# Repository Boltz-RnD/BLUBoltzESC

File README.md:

# DarkESC

A Remixed Board Design from The BlueESC with a large footprint and Utilizing easy to source components for a DIYer.

I've made this ESC Board Design for a College Project,but you can use it wherever however you want.

Although it may look a DIY Design but is no diffrent than a 60A version of BlueESC, It runs on a Forked Version of Simonk's TGY firmware.

Unlike other DIY ESC, This one is a lot more reliable and is much more Optimized (Thanks to the TGY Firmware). 

The Firmware for this ESC is same as that of BlueESC and can be found at https://github.com/bluerobotics/tgy

Feel Free to Contribute and develop A better smaller but still DIY-able ESC.

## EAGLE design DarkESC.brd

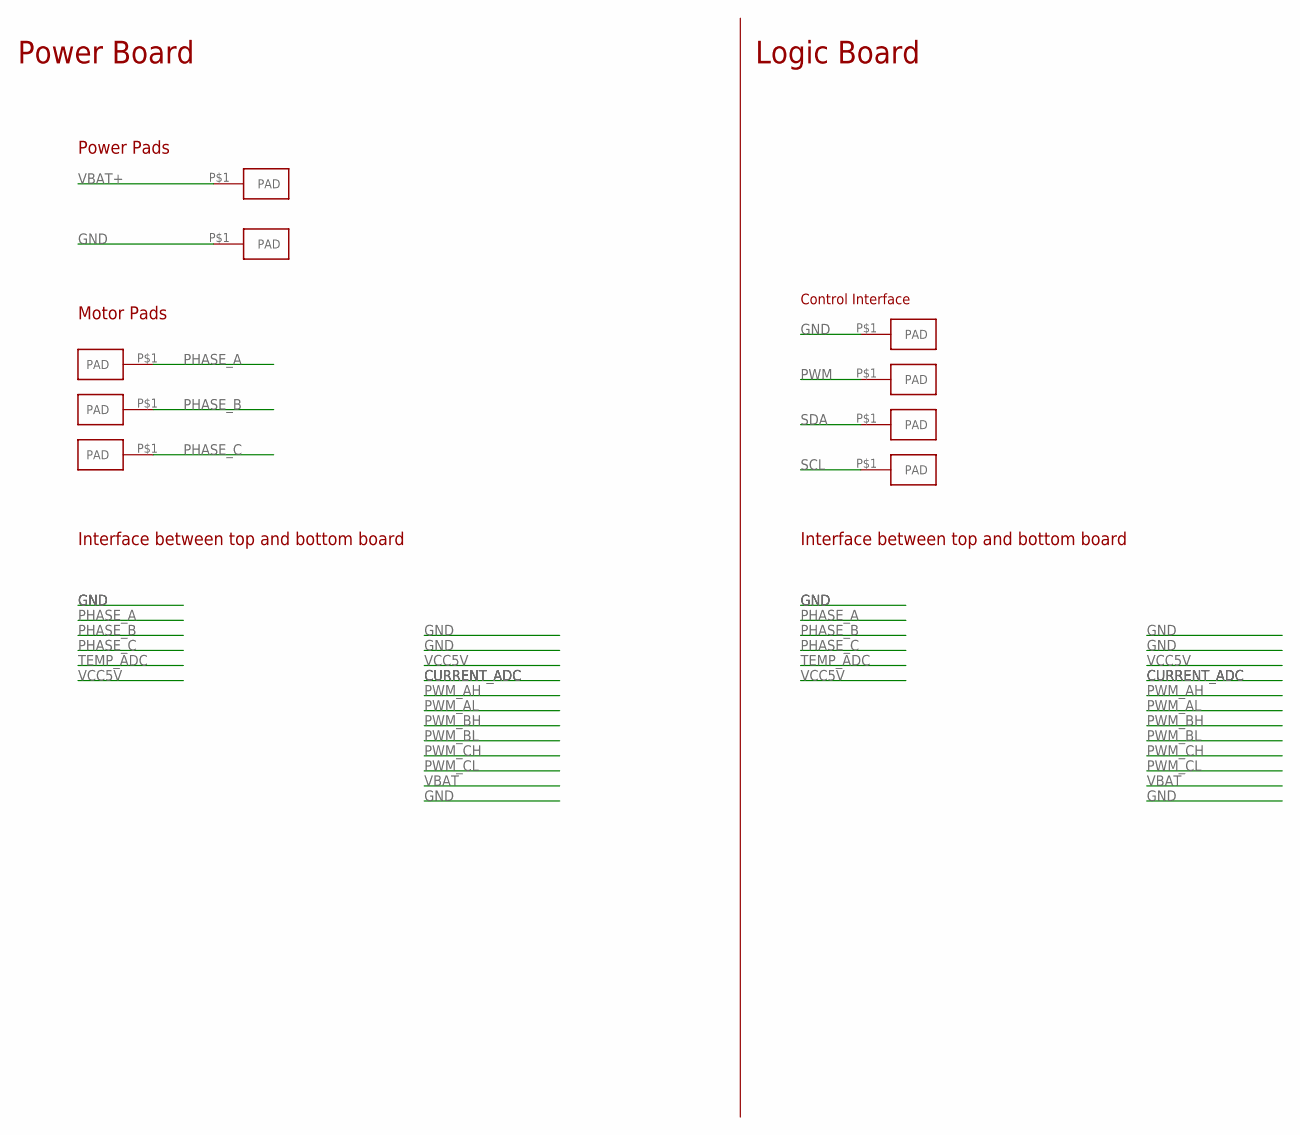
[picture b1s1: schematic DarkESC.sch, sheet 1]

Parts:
U$1, U$2: PADPTH-MED; PAD-PTH-MED-1
U$5, U$6, U$7: PAD18AWG; PAD-PTH-18AWG-1
U$11, U$12, U$13, U$14: PAD1.5X3MM; PAD-1.5X3MM

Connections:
GND: U$2.P$1, U$11.P$1; also elsewhere on the board
PHASE_A: U$5.P$1; also elsewhere on the board
PHASE_B: U$6.P$1; also elsewhere on the board
PHASE_C: U$7.P$1; also elsewhere on the board
PWM: U$14.P$1; also elsewhere on the board
SCL: U$13.P$1; also elsewhere on the board
SDA: U$12.P$1; also elsewhere on the board
VBAT+: U$1.P$1; also elsewhere on the board

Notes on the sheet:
Power Pads
Motor Pads
Interface between top and bottom board
Control Interface
Power Board
Logic Board

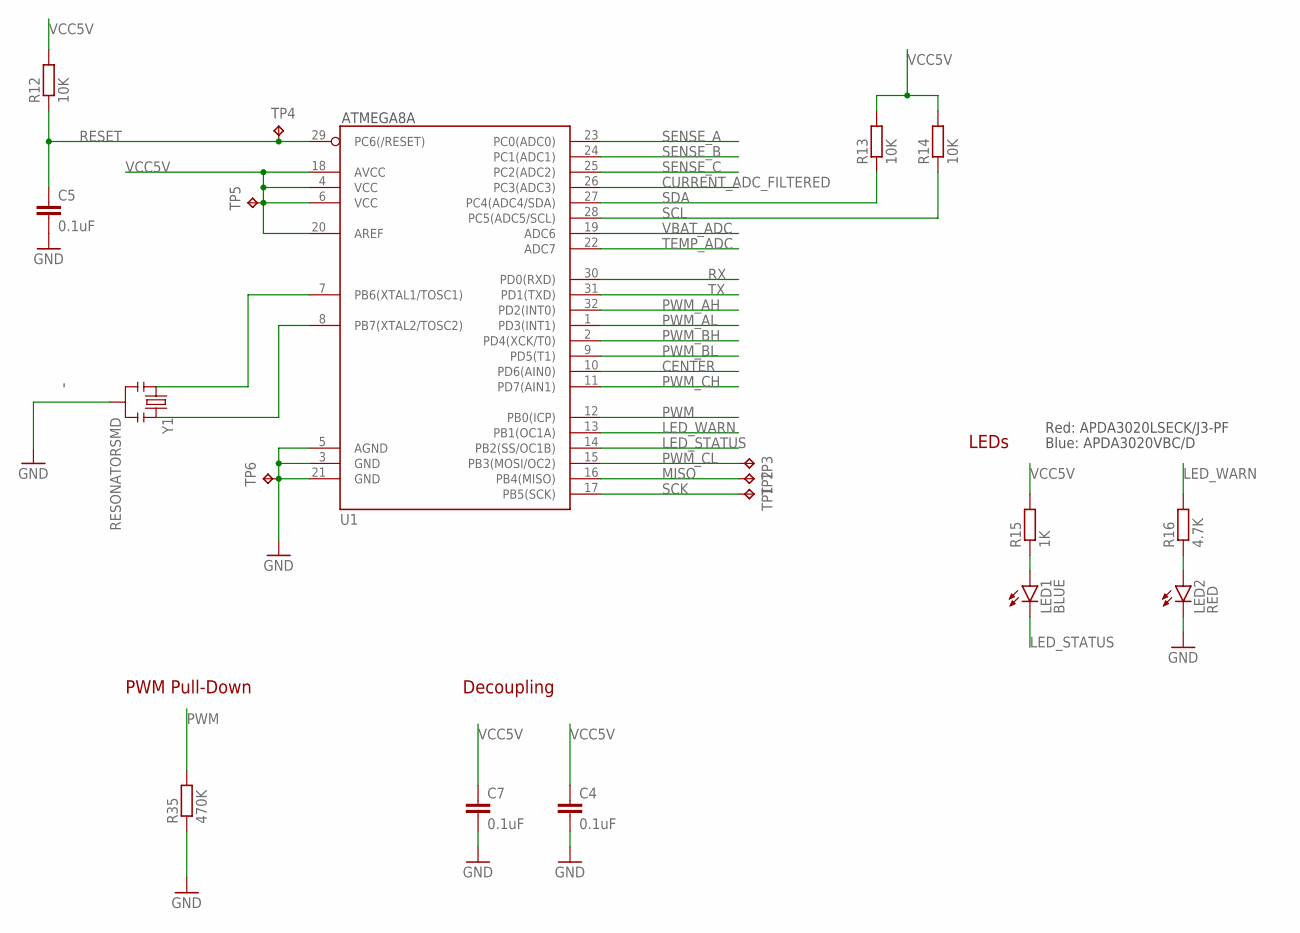
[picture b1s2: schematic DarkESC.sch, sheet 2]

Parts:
C4, C5, C7: 0.1uF; C3216
LED1: BLUE; SMT-LED-3X2-RA
LED2: RED; SMT-LED-3X2-RA
R12, R13, R14: 10K; R3216
R15: 1K; R3216
R16: 4.7K; R3216
R35: 470K; R3216
TP1, TP2, TP3, TP4, TP5, TP6: TPB1,27; B1,27
U1: ATMEGA168; TQFP32-08
Y1: RESONATORSMD; RESONATOR-SMD

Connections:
CENTER: U1.10 (PD6(AIN0)); also elsewhere on the board
CURRENT_ADC_FILTERED: U1.26 (PC3(ADC3)); also elsewhere on the board
GND: C4.2, C5.2, C7.2, LED2.2 (C), R35.1, TP6.TP, U1.3 (GND), U1.5 (AGND), U1.21 (GND), Y1.2; also elsewhere on the board
LED_STATUS: LED1.2 (C), U1.14 (PB2(SS/OC1B))
LED_WARN: R16.2, U1.13 (PB1(OC1A))
MISO: TP2.TP, U1.16 (PB4(MISO))
unnamed: LED2.1 (A), R16.1
unnamed: U1.7 (PB6(XTAL1/TOSC1)), Y1.1
unnamed: U1.8 (PB7(XTAL2/TOSC2)), Y1.3
unnamed: LED1.1 (A), R15.1
PWM: R35.2, U1.12 (PB0(ICP)); also elsewhere on the board
PWM_AH: U1.32 (PD2(INT0)); also elsewhere on the board
PWM_AL: U1.1 (PD3(INT1)); also elsewhere on the board
PWM_BH: U1.2 (PD4(XCK/T0)); also elsewhere on the board
PWM_BL: U1.9 (PD5(T1)); also elsewhere on the board
PWM_CH: U1.11 (PD7(AIN1)); also elsewhere on the board
PWM_CL: TP3.TP, U1.15 (PB3(MOSI/OC2)); also elsewhere on the board
RESET: C5.1, R12.1, TP4.TP, U1.29 (PC6(/RESET))
RX: U1.30 (PD0(RXD))
SCK: TP1.TP, U1.17 (PB5(SCK))
SCL: R14.1, U1.28 (PC5(ADC5/SCL)); also elsewhere on the board
SDA: R13.1, U1.27 (PC4(ADC4/SDA)); also elsewhere on the board
SENSE_A: U1.23 (PC0(ADC0)); also elsewhere on the board
SENSE_B: U1.24 (PC1(ADC1)); also elsewhere on the board
SENSE_C: U1.25 (PC2(ADC2)); also elsewhere on the board
TEMP_ADC: U1.22 (ADC7); also elsewhere on the board
TX: U1.31 (PD1(TXD))
VBAT_ADC: U1.19 (ADC6); also elsewhere on the board
VCC5V: C4.1, C7.1, R12.2, R13.2, R14.2, R15.2, TP5.TP, U1.4 (VCC), U1.6 (VCC), U1.18 (AVCC), U1.20 (AREF); also elsewhere on the board

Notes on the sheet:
ATMEGA8A
Decoupling
LEDs
Red: APDA3020LSECK/J3-PF
Blue: APDA3020VBC/D
PWM Pull-Down

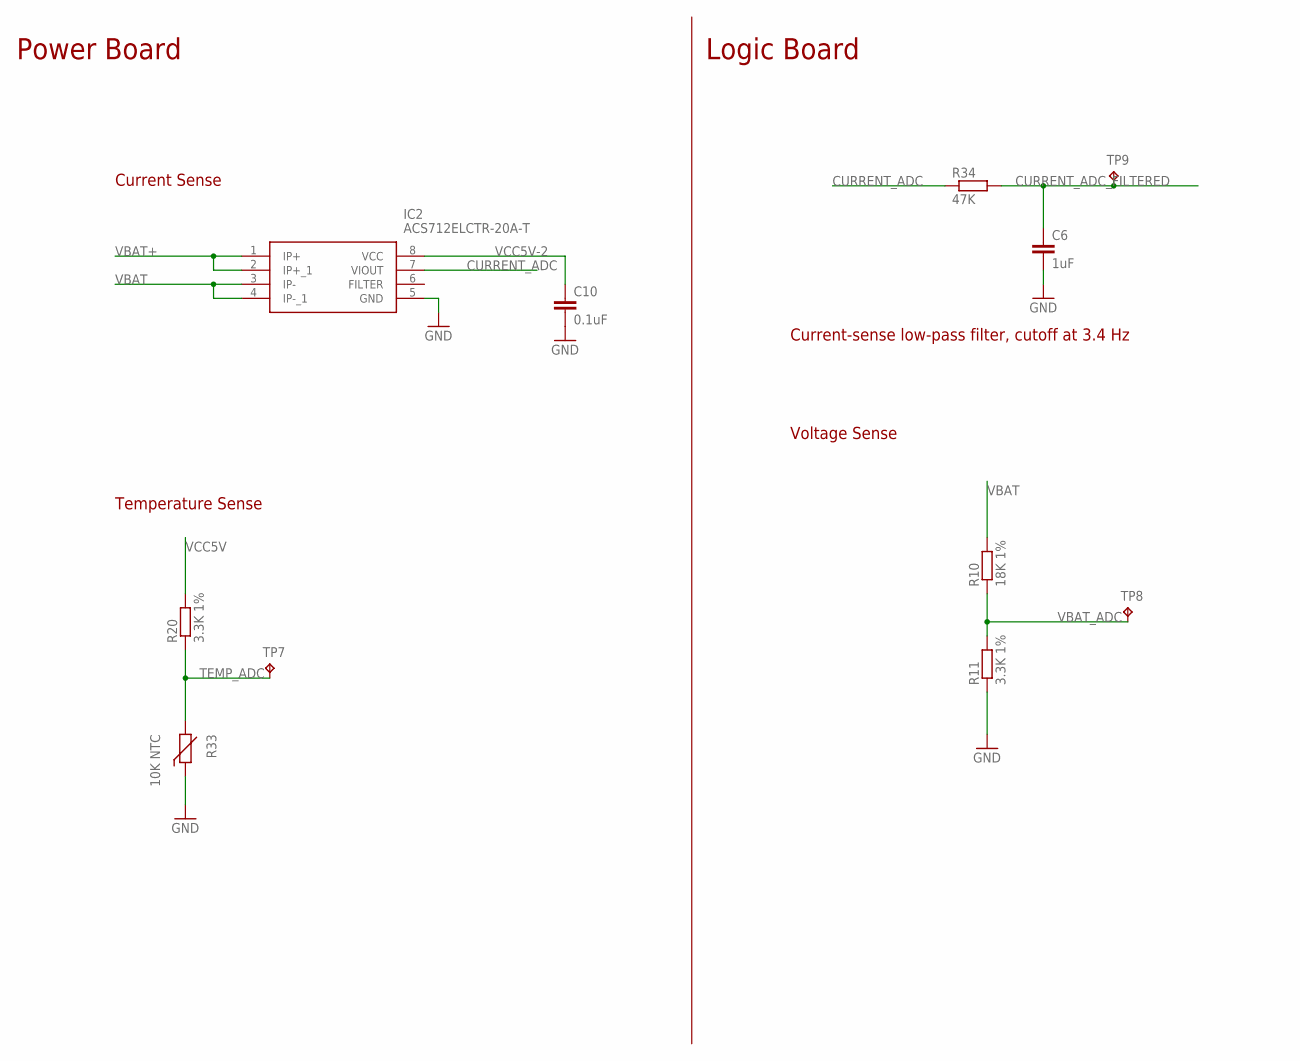
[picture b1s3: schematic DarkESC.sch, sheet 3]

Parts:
C6: 1uF; C3216
C10: 0.1uF; C3216
IC2: ACS712ELCTR-20A-T; SOIC127P600X175-8N
R10: 18K 1%; 0204/7
R11, R20: 3.3K 1%; 0204/7
R33: 10K NTC; RS-2,5
R34: 47K; R3216
TP7, TP8, TP9: TPB1,27; B1,27

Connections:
CURRENT_ADC: IC2.7 (VIOUT), R34.1
CURRENT_ADC_FILTERED: C6.1, R34.2, TP9.TP; also elsewhere on the board
GND: C6.2, C10.2, IC2.5 (GND), R11.1, R33.1; also elsewhere on the board
TEMP_ADC: R20.1, R33.2, TP7.TP; also elsewhere on the board
VBAT: IC2.3 (IP-), IC2.4 (IP-_1), R10.2; also elsewhere on the board
VBAT+: IC2.1 (IP+), IC2.2 (IP+_1); also elsewhere on the board
VBAT_ADC: R10.1, R11.2, TP8.TP; also elsewhere on the board
VCC5V: R20.2; also elsewhere on the board
VCC5V-2: C10.1, IC2.8 (VCC)

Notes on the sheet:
Power Board
Logic Board
Current-sense low-pass filter, cutoff at 3.4 Hz
Voltage Sense
Current Sense
Temperature Sense

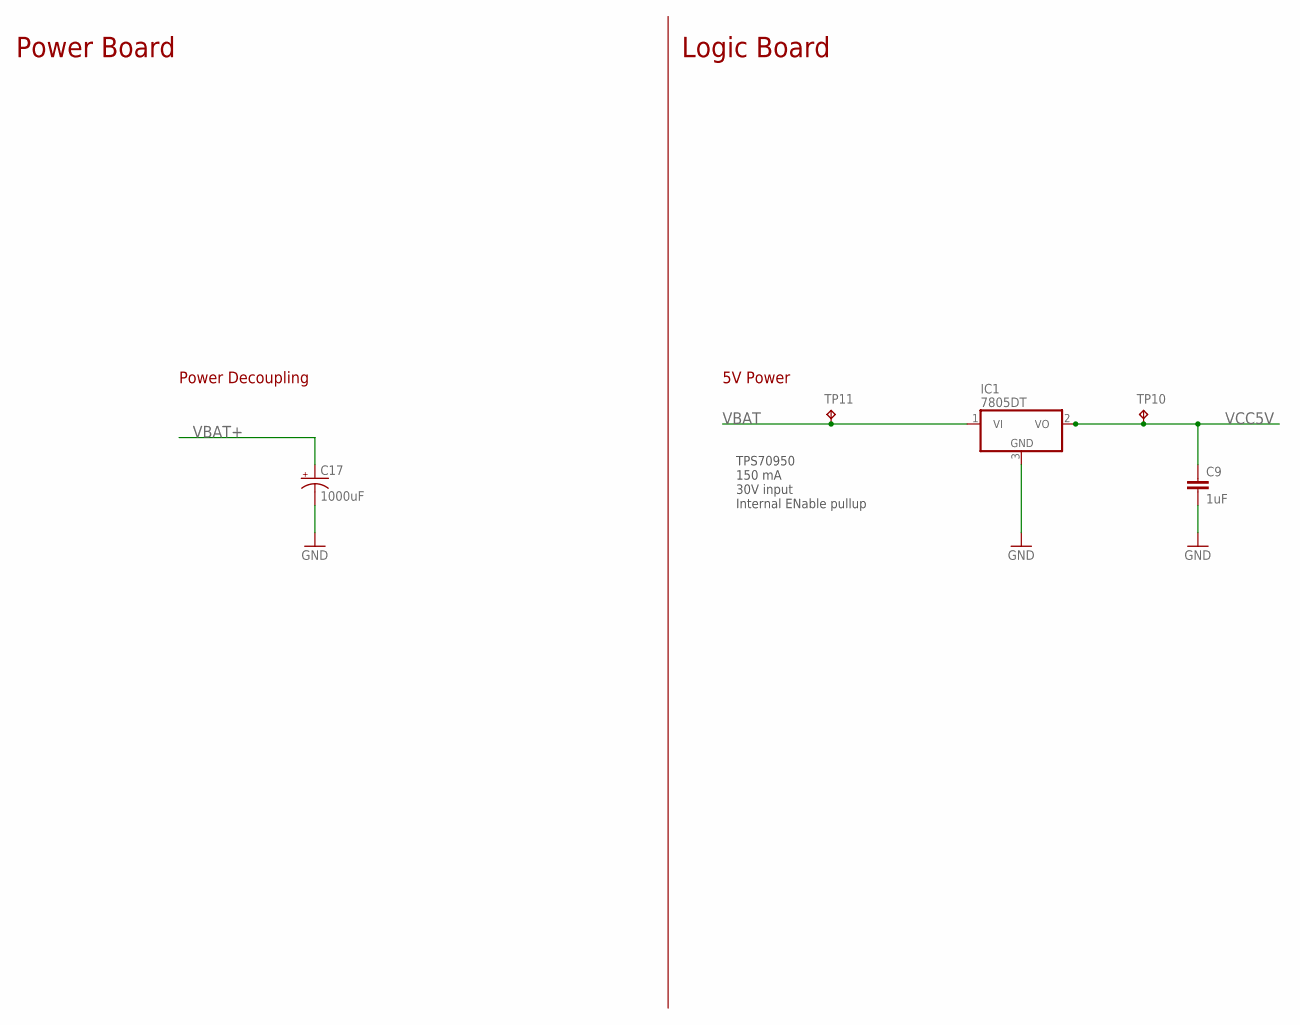
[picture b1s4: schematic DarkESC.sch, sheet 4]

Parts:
C9: 1uF; C3216
C17: 1000uF; CPOL-RADIAL-100UF-25V
IC1: 7805DT; TO252
TP10, TP11: TPB1,27; B1,27

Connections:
GND: C9.2, C17.2 (-), IC1.3 (GND); also elsewhere on the board
VBAT: IC1.1 (VI), TP11.TP; also elsewhere on the board
VBAT+: C17.1 (+); also elsewhere on the board
VCC5V: C9.1, IC1.2 (VO), TP10.TP; also elsewhere on the board

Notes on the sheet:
Power Board
Logic Board
Power Decoupling
5V Power
TPS70950 150 mA 30V input Internal ENable pullup

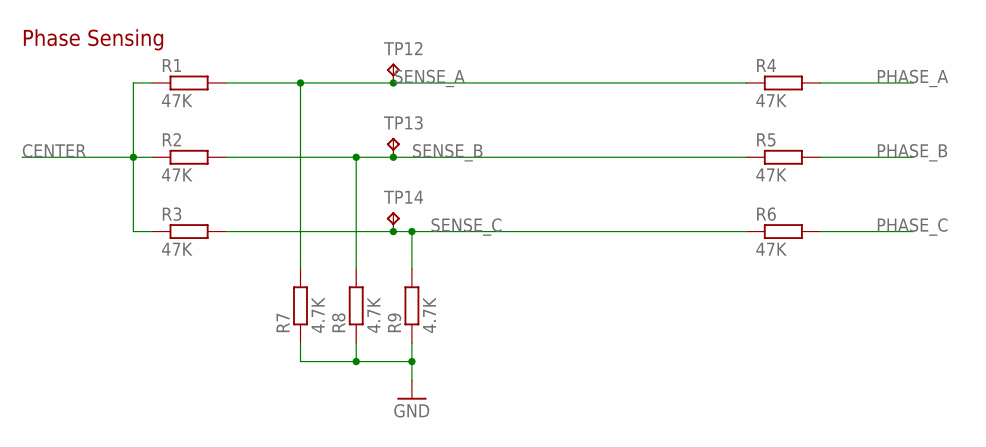
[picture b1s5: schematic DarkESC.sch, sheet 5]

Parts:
R1, R2, R3, R4, R5, R6: 47K; R3216
R7, R8, R9: 4.7K; R3216
TP12, TP13, TP14: TPB1,27; B1,27

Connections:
CENTER: R1.1, R2.1, R3.1; also elsewhere on the board
GND: R7.1, R8.1, R9.1; also elsewhere on the board
PHASE_A: R4.2; also elsewhere on the board
PHASE_B: R5.2; also elsewhere on the board
PHASE_C: R6.2; also elsewhere on the board
SENSE_A: R1.2, R4.1, R7.2, TP12.TP; also elsewhere on the board
SENSE_B: R2.2, R5.1, R8.2, TP13.TP; also elsewhere on the board
SENSE_C: R3.2, R6.1, R9.2, TP14.TP; also elsewhere on the board

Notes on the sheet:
Phase Sensing

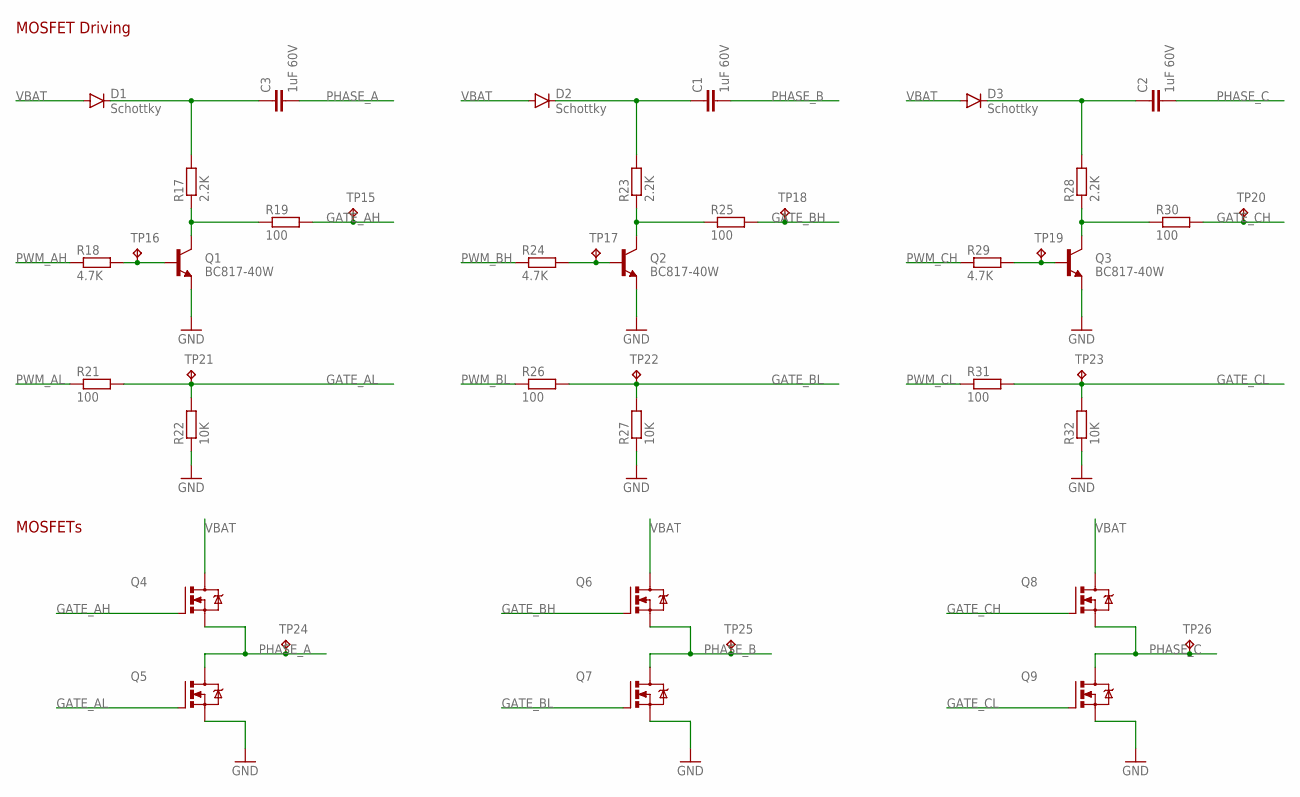
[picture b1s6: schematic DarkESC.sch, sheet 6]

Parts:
C1, C2, C3: 1uF 60V; C3216
D1, D2, D3: Schottky; SMB-DIODE
Q1, Q2, Q3: BC817-40W; SOT23
Q4, Q5, Q6, Q7, Q8, Q9: IRF520; TO220BV
R17, R23, R28: 2.2K; R3216
R18, R24, R29: 4.7K; R3216
R19, R21, R25, R26, R30, R31: 100; R3216
R22, R27, R32: 10K; R3216
TP15, TP16, TP17, TP18, TP19, TP20, TP21, TP22, TP23, TP24, TP25, TP26: TPB1,27; B1,27

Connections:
GATE_AH: Q4.G, R19.2, TP15.TP
GATE_AL: Q5.G, R21.2, R22.2, TP21.TP
GATE_BH: Q6.G, R25.2, TP18.TP
GATE_BL: Q7.G, R26.2, R27.2, TP22.TP
GATE_CH: Q8.G, R30.2, TP20.TP
GATE_CL: Q9.G, R31.2, R32.2, TP23.TP
GND: Q1.2 (E), Q2.2 (E), Q3.2 (E), Q5.S, Q7.S, Q9.S, R22.1, R27.1, R32.1; also elsewhere on the board
unnamed: Q1.1 (B), R18.2, TP16.TP
unnamed: Q1.3 (C), R17.1, R19.1
unnamed: Q2.1 (B), R24.2, TP17.TP
unnamed: Q2.3 (C), R23.1, R25.1
unnamed: Q3.1 (B), R29.2, TP19.TP
unnamed: Q3.3 (C), R28.1, R30.1
unnamed: C3.1, D1.C, R17.2
unnamed: C1.1, D2.C, R23.2
unnamed: C2.1, D3.C, R28.2
PHASE_A: C3.2, Q4.S, Q5.D, TP24.TP; also elsewhere on the board
PHASE_B: C1.2, Q6.S, Q7.D, TP25.TP; also elsewhere on the board
PHASE_C: C2.2, Q8.S, Q9.D, TP26.TP; also elsewhere on the board
PWM_AH: R18.1; also elsewhere on the board
PWM_AL: R21.1; also elsewhere on the board
PWM_BH: R24.1; also elsewhere on the board
PWM_BL: R26.1; also elsewhere on the board
PWM_CH: R29.1; also elsewhere on the board
PWM_CL: R31.1; also elsewhere on the board
VBAT: D1.A, D2.A, D3.A, Q4.D, Q6.D, Q8.D; also elsewhere on the board

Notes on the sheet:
MOSFETs
MOSFET Driving

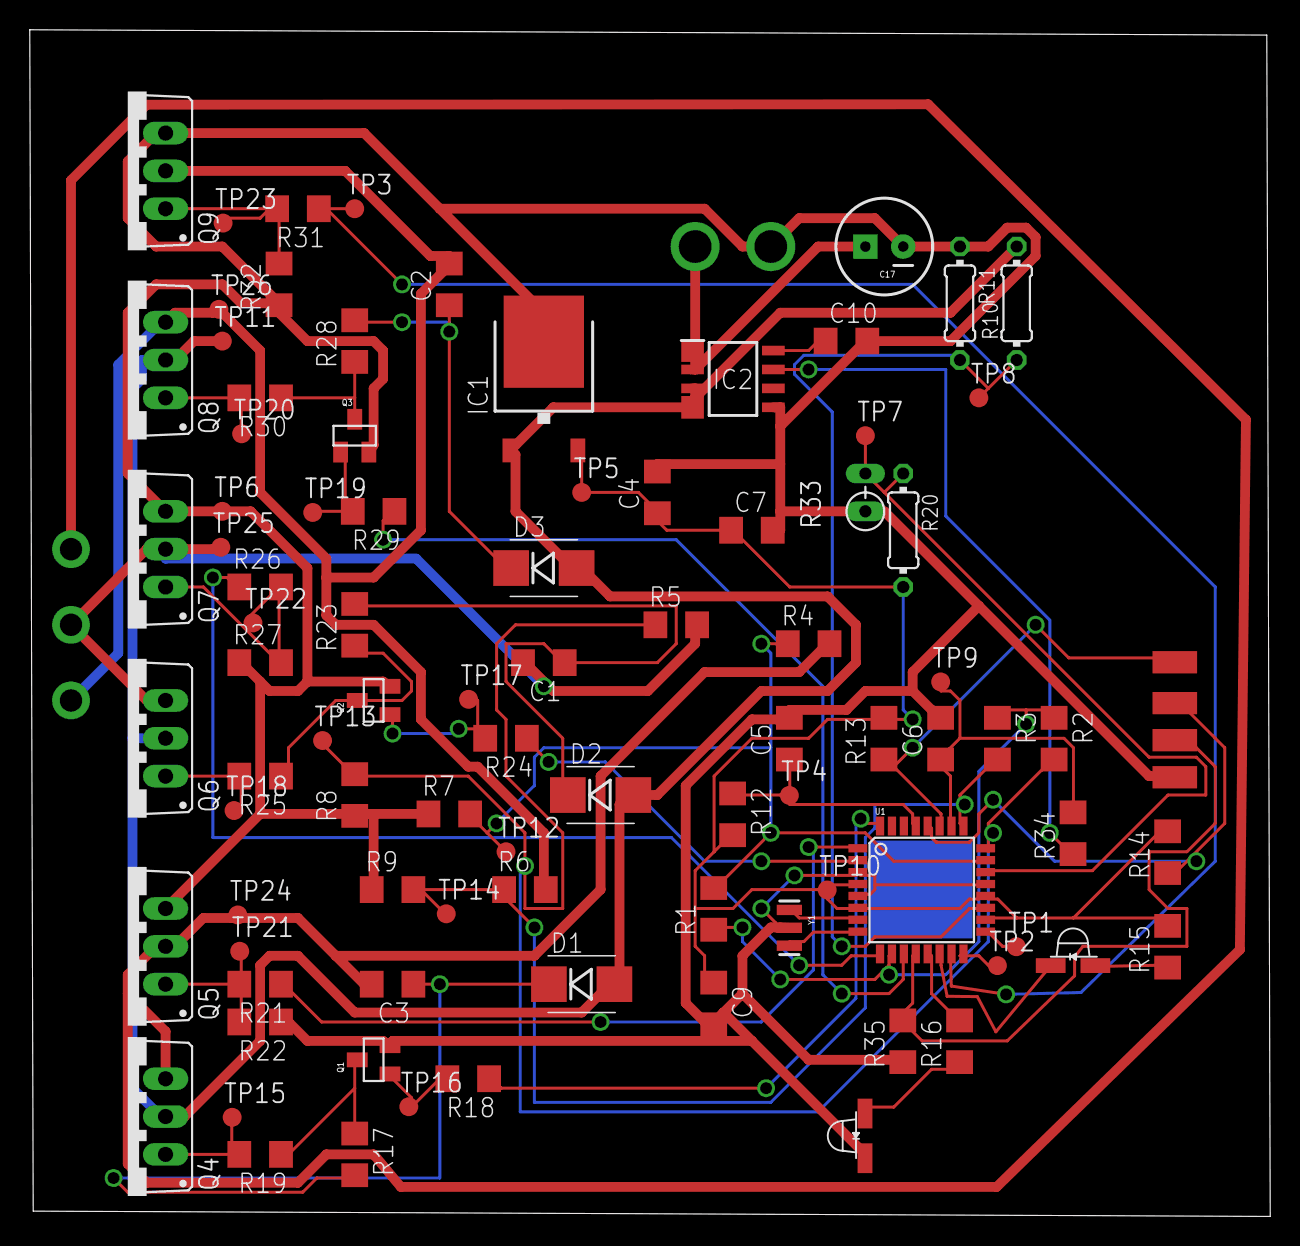
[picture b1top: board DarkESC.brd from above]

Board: 2 copper layers, 83.3 x 79.7 mm, 98 parts (0 on the bottom side), 49 nets.

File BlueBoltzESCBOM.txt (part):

Part Value          Device               Package          Description                                
C1   1uF 60V        C-US025-040X050      C025-040X050     CAPACITOR, American symbol                 
C2   1uF 60V        C-US025-040X050      C025-040X050     CAPACITOR, American symbol                 
C3   1uF 60V        C-US025-040X050      C025-040X050     CAPACITOR, American symbol                 
C4   0.1uF          CPOL-USE2.5-6        E2,5-6           POLARIZED CAPACITOR, American symbol       
C5   0.1uF          C-US025-030X050      C025-030X050     CAPACITOR, American symbol                 
C6   1uF            C-US025-030X050      C025-030X050     CAPACITOR, American symbol                 
C7   0.1uF          CPOL-USE2.5-6        E2,5-6           POLARIZED CAPACITOR, American symbol       
C8   2.2pF          C2.5/5               C2.5-5           CAPACITOR                                  
C9   1uF            CPOL-USE2.5-7        E2,5-7           POLARIZED CAPACITOR, American symbol       
C10  0.1uF          C-US025-030X050      C025-030X050     CAPACITOR, American symbol                 
C11  100uF          CPOL-USE3.5-8        E3,5-8           POLARIZED CAPACITOR, American symbol       
C12  2.2pF          C2.5/5               C2.5-5           CAPACITOR                                  
C15  100uF          CPOL-USE3.5-8        E3,5-8           POLARIZED CAPACITOR, American symbol       
C16  100uF          CPOL-USE3.5-8        E3,5-8           POLARIZED CAPACITOR, American symbol       
C17  100uF          CPOL-USE3.5-8        E3,5-8           POLARIZED CAPACITOR, American symbol       
D1   Schottky       SCHOTTKY-DIODEDO35-7 DO35-7           Schottky Diode                             
D2   Schottky       SCHOTTKY-DIODEDO35-7 DO35-7           Schottky Diode                             
D3   Schottky       SCHOTTKY-DIODEDO35-7 DO35-7           Schottky Diode                             
IC1  7805TV         7805TV               TO220V           Positive VOLTAGE REGULATOR                 
LED1 BLUE           LED3X2-RA            SMT-LED-3X2-RA   LEDs                                       
LED2 RED            LED3X2-RA            SMT-LED-3X2-RA   LEDs                                       
Q1   BD679          BD679                TO126AV          NPN DARLINGTON TRANSISTOR                  
Q2   BD679          BD679                TO126AV          NPN DARLINGTON TRANSISTOR                  
Q3   BD679          BD679                TO126AV          NPN DARLINGTON TRANSISTOR                  
Q4   IRLZ44Z        IRLZ44Z              TO220BH          N-Channel HEXFET® Power MOSFET Logic Level 
Q5   IRLZ44Z        IRLZ44Z              TO220BH          N-Channel HEXFET® Power MOSFET Logic Level 
Q6   IRLZ44Z        IRLZ44Z              TO220BH          N-Channel HEXFET® Power MOSFET Logic Level 
Q7   IRLZ44Z        IRLZ44Z              TO220BH          N-Channel HEXFET® Power MOSFET Logic Level 
Q8   IRLZ44Z        IRLZ44Z              TO220BH          N-Channel HEXFET® Power MOSFET Logic Level 
Q9   IRLZ44Z        IRLZ44Z              TO220BH          N-Channel HEXFET® Power MOSFET Logic Level 
Q10                 XTAL/S               QS               CRYSTAL                                    
R1   47K            R-US_0207/10         0207/10          RESISTOR, American symbol                  
R2   47K            R-US_0207/10         0207/10          RESISTOR, American symbol                  
R3   47K            R-US_0207/10         0207/10          RESISTOR, American symbol                  
R4   47K            R-US_0207/10         0207/10          RESISTOR, American symbol                  
R5   47K            R-US_0207/10         0207/10          RESISTOR, American symbol                  
R6   47K            R-US_0207/10         0207/10          RESISTOR, American symbol                  
R7   4.7K           R-US_0207/10         0207/10          RESISTOR, American symbol                  
R8   4.7K           R-US_0207/10         0207/10          RESISTOR, American symbol                  
R9   4.7K           R-US_0207/10         0207/10          RESISTOR, American symbol                  
R10  18K 1%         R-US_0207/10         0207/10          RESISTOR, American symbol                  
R11  3.3K 1%        R-US_0207/10         0207/10          RESISTOR, American symbol                  
R12  10K            R-US_M3216           M3216            RESISTOR, American symbol                  
R13  10K            R-US_M3216           M3216            RESISTOR, American symbol                  
R14  10K            R-US_M3216           M3216            RESISTOR, American symbol                  
R15  1K             R-US_M3216           M3216            RESISTOR, American symbol                  
R16  4.7K           R-US_0207/10         0207/10          RESISTOR, American symbol                  
R17  2.2K           R-US_0207/10         0207/10          RESISTOR, American symbol                  
R18  4.7K           R-US_0207/10         0207/10          RESISTOR, American symbol                  
R19  100            R-US_M3216           M3216            RESISTOR, American symbol                  
R20  3.3K 1%        R-US_0207/10         0207/10          RESISTOR, American symbol                  
R21  100            R-US_M3216           M3216            RESISTOR, American symbol                  
R22  10K            R-US_M3216           M3216            RESISTOR, American symbol                  
R23  2.2K           R-US_0207/10         0207/10          RESISTOR, American symbol                  
R24  4.7K           R-US_0207/10         0207/10          RESISTOR, American symbol                  
R25  100            R-US_M3216           M3216            RESISTOR, American symbol                  
R26  100            R-US_M3216           M3216            RESISTOR, American symbol                  
R27  10K            R-US_M3216           M3216            RESISTOR, American symbol                  
R28  2.2K           R-US_0207/10         0207/10          RESISTOR, American symbol                  
R29  4.7K           R-US_0207/10         0207/10          RESISTOR, American symbol                  
R30  100            R-US_M3216           M3216            RESISTOR, American symbol                  
R31  100            R-US_M3216           M3216            RESISTOR, American symbol                  
R32  10K            R-US_M3216           M3216            RESISTOR, American symbol                  
R33  10K NTC        33KOHM1/10W1%(0603)  0603-RES         RES-08416                                  
R34  47K            R-US_0207/10         0207/10          RESISTOR, American symbol                  
R35  470K           R-US_0207/10         0207/10          RESISTOR, American symbol                  
R36  0              R-EU_MELF0102R       MINI_MELF-0102R  RESISTOR, European symbol                  
R37  0              R-EU_MELF0102R       MINI_MELF-0102R  RESISTOR, European symbol                  
R38  0              R-EU_MELF0102R       MINI_MELF-0102R  RESISTOR, European symbol                  
R39  0              R-EU_MELF0102R       MINI_MELF-0102R  RESISTOR, European symbol                  
R40  0              R-EU_MELF0102R       MINI_MELF-0102R  RESISTOR, European symbol                  
U$1  PWR+           PADPTH-MED           PAD-PTH-MED-1                                               
U$2  PWR-           PADPTH-MED           PAD-PTH-MED-1                                               
U$3  ACS7XX12-WFQFN ACS7XX12-WFQFN       12-WFQFN                                                    
U$4  HEADER-62MM    HEADER-62MM          HEADER-2MM-6POS                                             
U$5  A              PAD18AWG             PAD-PTH-18AWG-1                                             
U$6  B              PAD18AWG             PAD-PTH-18AWG-1                                             
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
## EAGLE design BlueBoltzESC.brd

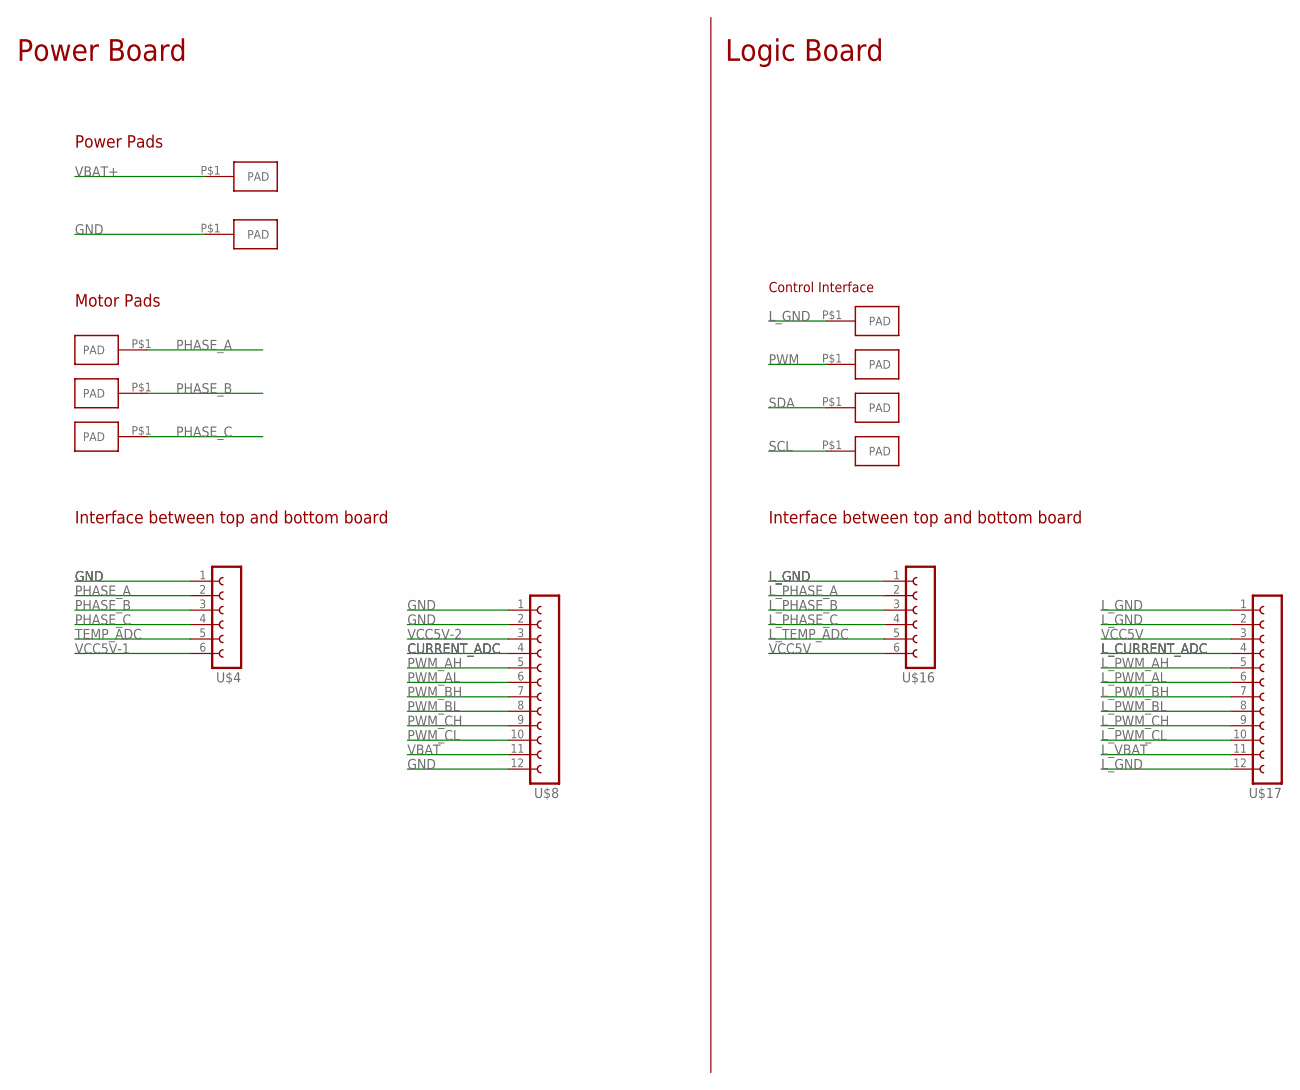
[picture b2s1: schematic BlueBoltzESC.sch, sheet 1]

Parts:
U$1: PWR+; PAD-PTH-MED-1
U$2: PWR-; PAD-PTH-MED-1
U$4, U$16: FE06-1; FE06
U$5: A; PAD-PTH-18AWG-1
U$6: B; PAD-PTH-18AWG-1
U$7: C; PAD-PTH-18AWG-1
U$8, U$17: FE12-1; FE12
U$11, U$12, U$13, U$14: PAD1.5X3MM; PAD-1.5X3MM

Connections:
CURRENT_ADC: U$8.4; also elsewhere on the board
GND: U$2.P$1, U$4.1, U$8.1, U$8.2, U$8.12; also elsewhere on the board
L_CURRENT_ADC: U$17.4; also elsewhere on the board
L_GND: U$11.P$1, U$16.1, U$17.1, U$17.2, U$17.12; also elsewhere on the board
L_PHASE_A: U$16.2; also elsewhere on the board
L_PHASE_B: U$16.3; also elsewhere on the board
L_PHASE_C: U$16.4; also elsewhere on the board
L_PWM_AH: U$17.5; also elsewhere on the board
L_PWM_AL: U$17.6; also elsewhere on the board
L_PWM_BH: U$17.7; also elsewhere on the board
L_PWM_BL: U$17.8; also elsewhere on the board
L_PWM_CH: U$17.9; also elsewhere on the board
L_PWM_CL: U$17.10; also elsewhere on the board
L_TEMP_ADC: U$16.5; also elsewhere on the board
L_VBAT: U$17.11; also elsewhere on the board
PHASE_A: U$4.2, U$5.P$1; also elsewhere on the board
PHASE_B: U$4.3, U$6.P$1; also elsewhere on the board
PHASE_C: U$4.4, U$7.P$1; also elsewhere on the board
PWM: U$14.P$1; also elsewhere on the board
PWM_AH: U$8.5; also elsewhere on the board
PWM_AL: U$8.6; also elsewhere on the board
PWM_BH: U$8.7; also elsewhere on the board
PWM_BL: U$8.8; also elsewhere on the board
PWM_CH: U$8.9; also elsewhere on the board
PWM_CL: U$8.10; also elsewhere on the board
SCL: U$13.P$1; also elsewhere on the board
SDA: U$12.P$1; also elsewhere on the board
TEMP_ADC: U$4.5; also elsewhere on the board
VBAT: U$8.11; also elsewhere on the board
VBAT+: U$1.P$1; also elsewhere on the board
VCC5V: U$16.6, U$17.3; also elsewhere on the board
VCC5V-1: U$4.6; also elsewhere on the board
VCC5V-2: U$8.3; also elsewhere on the board

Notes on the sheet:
Power Pads
Motor Pads
Interface between top and bottom board
Control Interface
Power Board
Logic Board

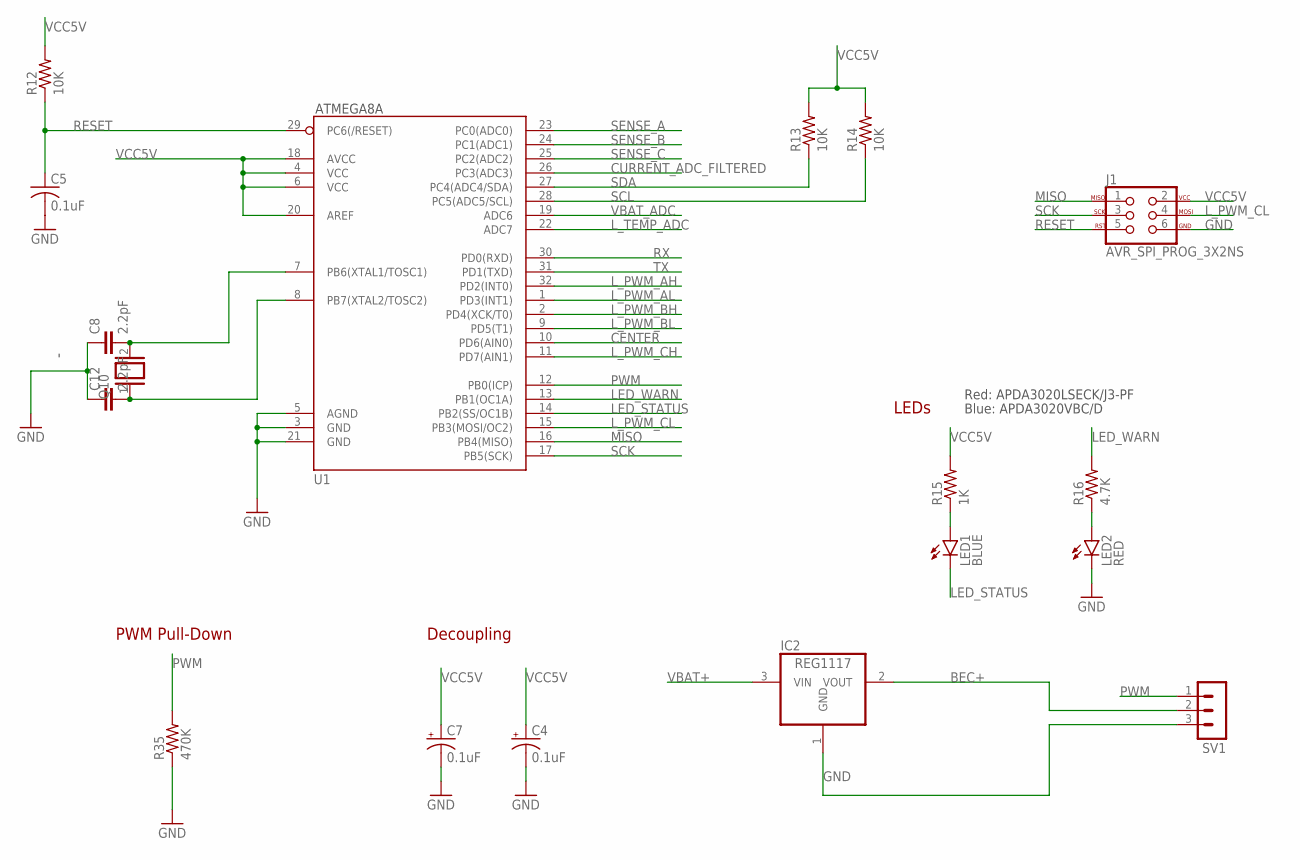
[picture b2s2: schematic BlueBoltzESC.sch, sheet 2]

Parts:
C4, C7: 0.1uF; E2,5-6
C5: 0.1uF; C025-030X050
C8, C12: 2.2pF; C2.5-5
IC2: REG1117; SOT223
J1: AVR_SPI_PROG_3X2NS; 2X3-NS
LED1: BLUE; SMT-LED-3X2-RA
LED2: RED; SMT-LED-3X2-RA
Q10: XTAL/S; QS
R12, R13, R14: 10K; M3216
R15: 1K; M3216
R16: 4.7K; 0207/10
R35: 470K; 0207/10
SV1: MA03-1
U1: ATMEGA168; TQFP32-08

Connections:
BEC+: IC2.2 (VOUT), SV1.2
CENTER: U1.10 (PD6(AIN0)); also elsewhere on the board
CURRENT_ADC_FILTERED: U1.26 (PC3(ADC3)); also elsewhere on the board
GND: IC2.1 (GND), J1.6, SV1.3; also elsewhere on the board
LED_STATUS: LED1.2 (C), U1.14 (PB2(SS/OC1B))
LED_WARN: R16.2, U1.13 (PB1(OC1A))
L_GND: C4.-, C5.2, C7.-, C8.1, C12.1, LED2.2 (C), R35.1, U1.3 (GND), U1.5 (AGND), U1.21 (GND); also elsewhere on the board
L_PWM_AH: U1.32 (PD2(INT0)); also elsewhere on the board
L_PWM_AL: U1.1 (PD3(INT1)); also elsewhere on the board
L_PWM_BH: U1.2 (PD4(XCK/T0)); also elsewhere on the board
L_PWM_BL: U1.9 (PD5(T1)); also elsewhere on the board
L_PWM_CH: U1.11 (PD7(AIN1)); also elsewhere on the board
L_PWM_CL: J1.4, U1.15 (PB3(MOSI/OC2)); also elsewhere on the board
L_TEMP_ADC: U1.22 (ADC7); also elsewhere on the board
MISO: J1.1, U1.16 (PB4(MISO))
unnamed: LED2.1 (A), R16.1
unnamed: C8.2, Q10.2, U1.7 (PB6(XTAL1/TOSC1))
unnamed: C12.2, Q10.1, U1.8 (PB7(XTAL2/TOSC2))
unnamed: LED1.1 (A), R15.1
PWM: R35.2, SV1.1, U1.12 (PB0(ICP)); also elsewhere on the board
RESET: C5.1, J1.5, R12.1, U1.29 (PC6(/RESET))
RX: U1.30 (PD0(RXD))
SCK: J1.3, U1.17 (PB5(SCK))
SCL: R14.1, U1.28 (PC5(ADC5/SCL)); also elsewhere on the board
SDA: R13.1, U1.27 (PC4(ADC4/SDA)); also elsewhere on the board
SENSE_A: U1.23 (PC0(ADC0)); also elsewhere on the board
SENSE_B: U1.24 (PC1(ADC1)); also elsewhere on the board
SENSE_C: U1.25 (PC2(ADC2)); also elsewhere on the board
TX: U1.31 (PD1(TXD))
VBAT+: IC2.3 (VIN); also elsewhere on the board
VBAT_ADC: U1.19 (ADC6); also elsewhere on the board
VCC5V: C4.+, C7.+, J1.2, R12.2, R13.2, R14.2, R15.2, U1.4 (VCC), U1.6 (VCC), U1.18 (AVCC), U1.20 (AREF); also elsewhere on the board

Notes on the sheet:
ATMEGA8A
Decoupling
LEDs
Red: APDA3020LSECK/J3-PF
Blue: APDA3020VBC/D
PWM Pull-Down

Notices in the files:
parts and their libraries:
SparkFun-DigitalIC: Licensing: Creative Commons ShareAlike 4.0 International - https://creativecommons.org/licenses/by-sa/4.0
